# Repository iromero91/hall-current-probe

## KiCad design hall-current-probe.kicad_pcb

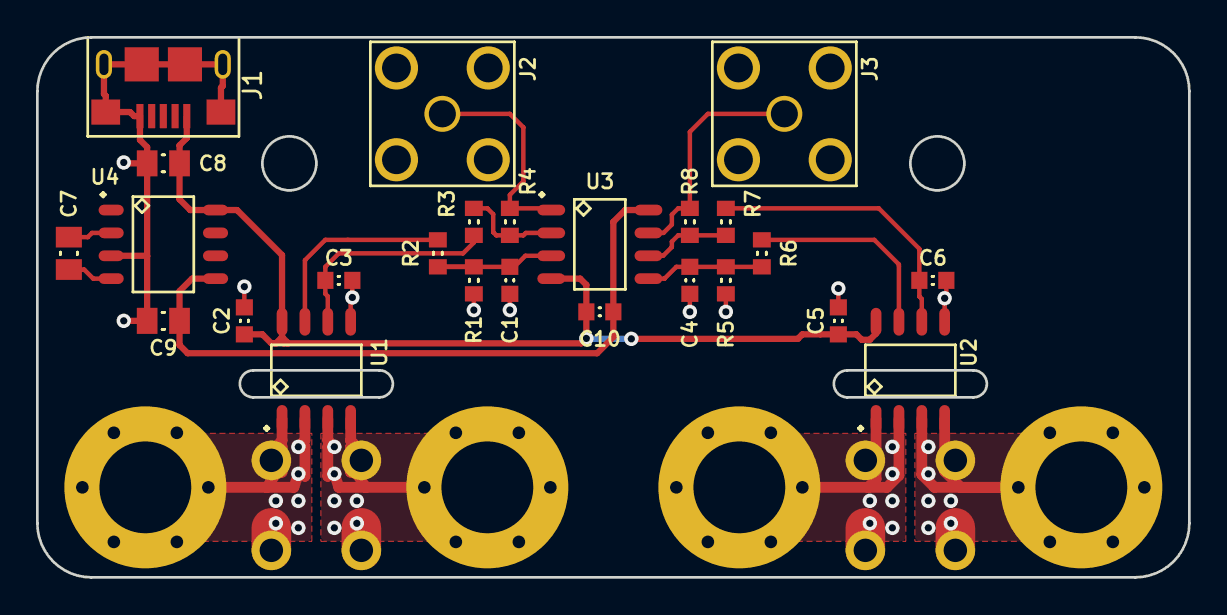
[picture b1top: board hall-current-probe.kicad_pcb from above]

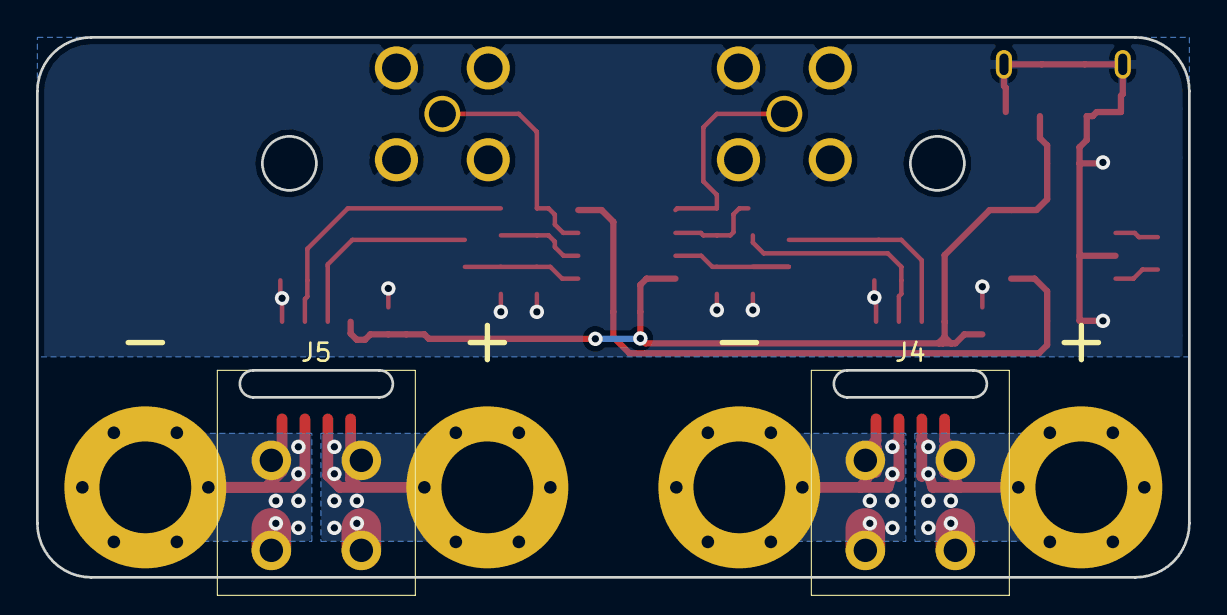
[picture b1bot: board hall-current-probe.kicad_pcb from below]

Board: 2 copper layers, 64.0 x 30.0 mm, 31 parts (6 on the bottom side), 19 nets.

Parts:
C1, C4: 100pF; CAPC1608X55
C2, C5, C10: 100nF; CAPC1608X55
C3, C6: 1nF; CAPC1608X55
C7, C8, C9: 10uF; CAPC2012X70
J1: USB; FCI_10118193-0001LF
J2, J3: CONN-SMA; CONN-TE-1814400
J4, J5: 2834076-1; TE_2834076-1
MP1, MP2, MP3, MP4: SCREW; SCREW-5-SUPPORTED
R1, R2, R3, R4, R5, R6, R7, R8: 10k; RESC1608X50
U1, U2: ACS730; SOIC127P600X175-8
U3: MC33078D; SOIC127P600X175-8
U4: LMC7660; SOIC127P620X170-8

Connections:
+5: C2.1, C5.1, C8.1, C10.1, J1.1, U1.8, U2.8, U3.4, U4.8
-5: C9.1, C10.2, U3.8, U4.5
/IA+: J4.2, MP1.1, U1.1, U1.2
/IA-: J4.1, MP2.1, U1.3, U1.4
/IB+: J5.2, MP3.1, U2.1, U2.2
/IB-: J5.1, MP4.1, U2.3, U2.4
/OUT_A: J2.1, R4.1, U3.1
/OUT_B: J3.1, R8.1, U3.7
GND: C1.2, C2.2, C3.2, C4.2, C5.2, C6.2, C8.2, C9.2, J1.5, J1.SH, J2.2, J3.2, R1.2, R5.2, U1.5, U2.5, U4.3
unnamed: C1.1, R1.1, R2.1, U3.3
unnamed: C3.1, R3.2, U1.6
unnamed: C4.1, R5.1, R6.1, U3.5
unnamed: C6.1, R7.2, U2.6
unnamed: C7.1, U4.2
unnamed: C7.2, U4.4
unnamed: R2.2, U1.7
unnamed: R3.1, R4.2, U3.2
unnamed: R6.2, U2.7
unnamed: R7.1, R8.2, U3.6

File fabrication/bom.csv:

qty,refs,description,package,manufacturer,MPN
2,"U1, U2",Allegro ACS730KLCTR-20AB-T,,Allegro,ACS730KLCTR-20AB-T
3,"C2, C5, C10",CAP MLCC 100nF X5R 50V [0603],0603 (1608 Metric),Taiyo Yuden,UMK107BJ104KAHT
2,"C1, C4",CAP MLCC 100pF C0G 50V [0603],0603 (1608 Metric),Johanson,500R14N101JV4T
3,"C7, C8, C9",CAP MLCC 10uF X5R 10V [0805],0805 (2012 Metric),Taiyo Yuden,LMK212BJ106KG-T 
2,"C3, C6",CAP MLCC 1nF C0G 25V [0603],0603 (1608 Metric),Yageo,CC0603JRNPO8BN102
1,J1,CONN FCI 10118193-0001LF,,Fci,10118193-0001LF
2,"J2, J3",CONN SMA,,Ebay,DSMAF14155L
2,"J4, J5",CONN TE 2834076-1,,Te,2834076-1
8,"R4, R3, R2, R1, R8, R7, R6, R5",RES SMD 10k 1% [0603],0603 (1608 Metric),Bourns,CR0603-FX-1002ELF
1,U4,TI LMC7660IMX/NOPB,,TI,LMC7660IMX/NOPB
1,U3,TI MC33078DR,,TI,MC33078DR

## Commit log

2018-06-24 Initial commit, first rev
2018-06-25 Update library
2018-06-28 Fix ERC and BOM issues
2018-06-28 More setup for fabrication
2018-06-28 Release to manufacture, version 1.0
